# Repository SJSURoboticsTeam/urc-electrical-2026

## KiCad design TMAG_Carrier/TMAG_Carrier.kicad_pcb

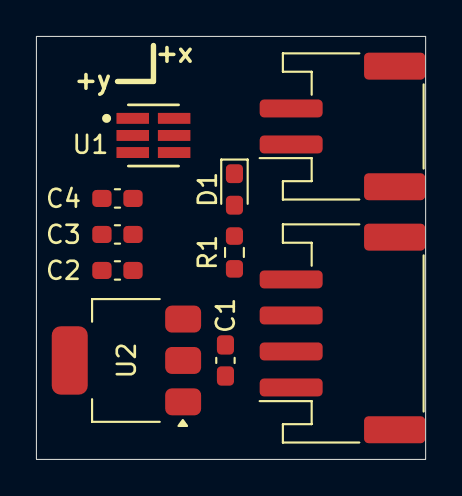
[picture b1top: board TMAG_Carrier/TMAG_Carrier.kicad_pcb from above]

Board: 2 copper layers, 21.6 x 23.5 mm, 10 parts (0 on the bottom side), 6 nets, no tracks yet.

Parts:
C1: 10u; C_0603_1608Metric_Pad1.08x0.95mm_HandSolder
C2: 22u; C_0603_1608Metric_Pad1.08x0.95mm_HandSolder
C3: 100n; C_0603_1608Metric_Pad1.08x0.95mm_HandSolder
C4: 1u; C_0603_1608Metric_Pad1.08x0.95mm_HandSolder
CanIn1: Conn_01x04_MountingPin; JST_PH_S4B-PH-SM4-TB_1x04-1MP_P2.00mm_Horizontal
D1: LED; LED_0603_1608Metric_Pad1.05x0.95mm_HandSolder
I2CIn1: Conn_01x02_MountingPin; JST_PH_S2B-PH-SM4-TB_1x02-1MP_P2.00mm_Horizontal
R1: 4.7k; R_0603_1608Metric_Pad0.98x0.95mm_HandSolder
U1: TMAG5273B1QDBVR; DBV0006A-IPC_A
U2: AMS1117-3.3; SOT-223-3_TabPin2

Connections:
+3V3: C2.1, C3.1, C4.1, R1.1, U1.4 (VCC), U2.2 (VO)
+5V: C1.1, CanIn1.1, U2.3 (VI)
GND: C1.2, C2.2, C3.2, C4.2, CanIn1.2, CanIn1.MP (MountPin), D1.1 (K), I2CIn1.MP (MountPin), U1.2 (TEST), U1.3 (GND), U1.5 (INT_N), U2.1 (GND)
I2C_SCL: I2CIn1.1, U1.1 (SCL)
I2C_SDA: I2CIn1.2, U1.6 (SDA)
unnamed: D1.2 (A), R1.2

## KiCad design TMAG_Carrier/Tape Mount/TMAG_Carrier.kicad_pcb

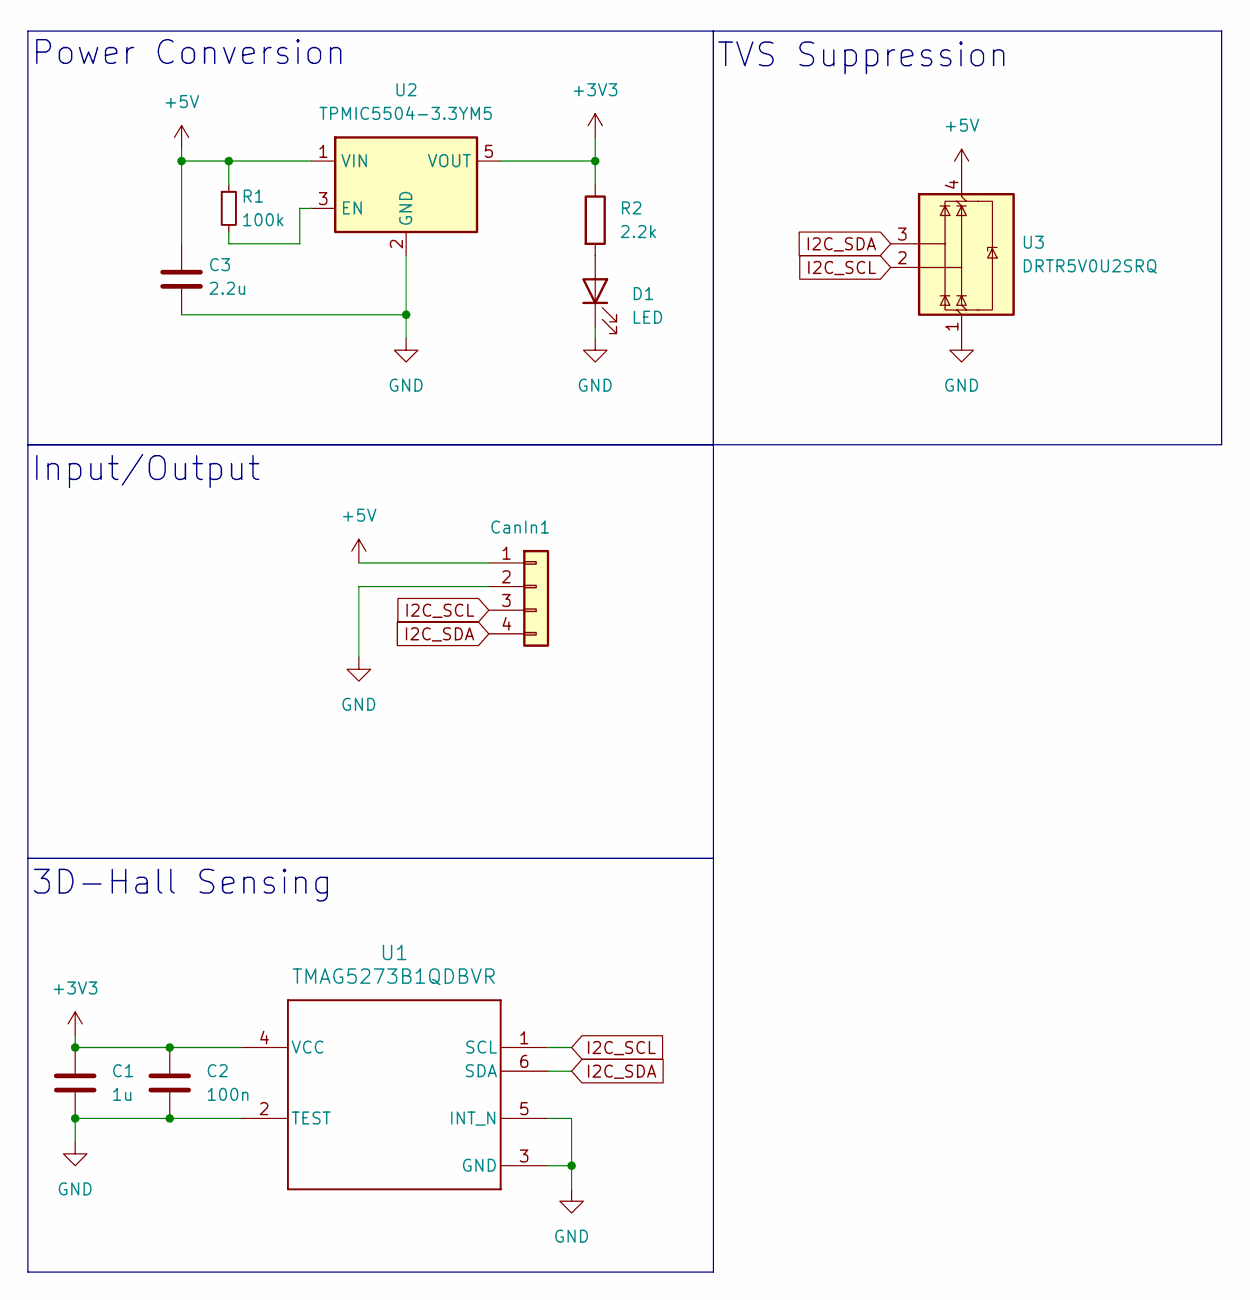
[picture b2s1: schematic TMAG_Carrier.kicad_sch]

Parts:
C1: 1u; C_0603_1608Metric_Pad1.08x0.95mm_HandSolder
C2: 100n; C_0603_1608Metric_Pad1.08x0.95mm_HandSolder
C3: 2.2u; C_0603_1608Metric_Pad1.08x0.95mm_HandSolder
CanIn1: Conn_01x04_MountingPin; Pluggable_Terminal_2.54mm_4P_Horizontal
D1: LED; LED_0603_1608Metric_Pad1.05x0.95mm_HandSolder
R1: 100k; R_0603_1608Metric_Pad0.98x0.95mm_HandSolder
R2: 2.2k; R_0603_1608Metric_Pad0.98x0.95mm_HandSolder
U1: TMAG5273B1QDBVR; DBV0006A-IPC_A
U2: TPMIC5504-3.3YM5; SOT-23-5
U3: DRTR5V0U2SRQ; SOT-143_Handsoldering

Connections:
+3V3: C1.1, C2.1, R2.1, U1.4 (VCC), U2.5 (VOUT)
+5V: C3.1, CanIn1.1, R1.1, U2.1 (VIN), U3.4 (VCC)
GND: C1.2, C2.2, C3.2, CanIn1.2, D1.1 (K), U1.2 (TEST), U1.3 (GND), U1.5 (INT_N), U2.2 (GND), U3.1 (GND)
I2C_SCL: CanIn1.3, U1.1 (SCL), U3.2 (I/O3)
I2C_SDA: CanIn1.4, U1.6 (SDA), U3.3 (I/O2)
unnamed: D1.2 (A), R2.2
unnamed: R1.2, U2.3 (EN)

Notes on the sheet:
Power Conversion
TVS Suppression
3D-Hall Sensing
Input/Output

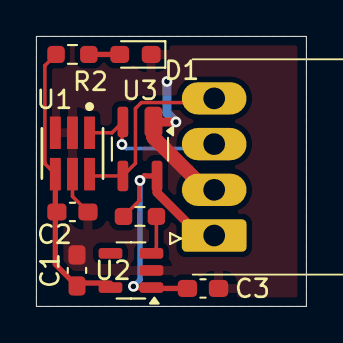
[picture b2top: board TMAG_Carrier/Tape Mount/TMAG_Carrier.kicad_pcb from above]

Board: 2 copper layers, 15.0 x 15.0 mm, 10 parts (0 on the bottom side), 7 nets.

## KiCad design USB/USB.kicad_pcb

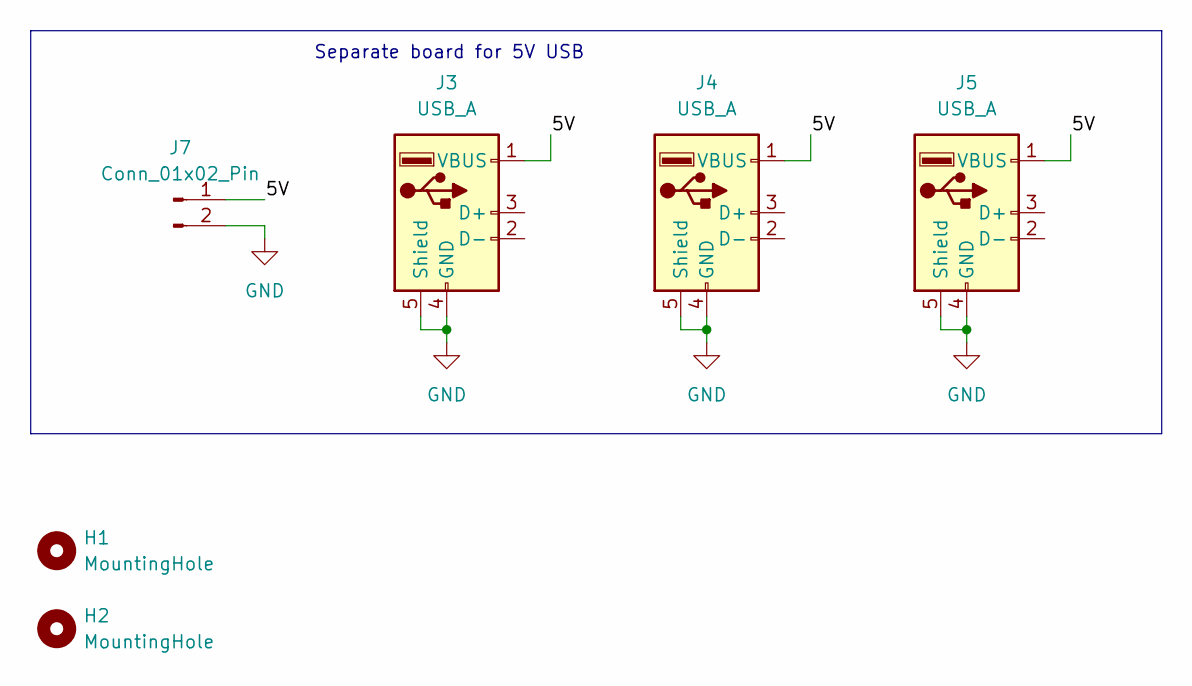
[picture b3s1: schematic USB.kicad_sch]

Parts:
H1, H2: MountingHole; MountingHole_3.2mm_M3_DIN965
J3, J4, J5: USB_A; USB_A_Molex_67643_Horizontal
J7: Conn_01x02_Pin; Pluggable_Terminal_2.54mm_2P_Horizontal

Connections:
/5V: J3.1 (VBUS), J4.1 (VBUS), J5.1 (VBUS), J7.1
GND: J3.4 (GND), J3.5 (Shield), J4.4 (GND), J4.5 (Shield), J5.4 (GND), J5.5 (Shield), J7.2

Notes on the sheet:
Separate board for 5V USB

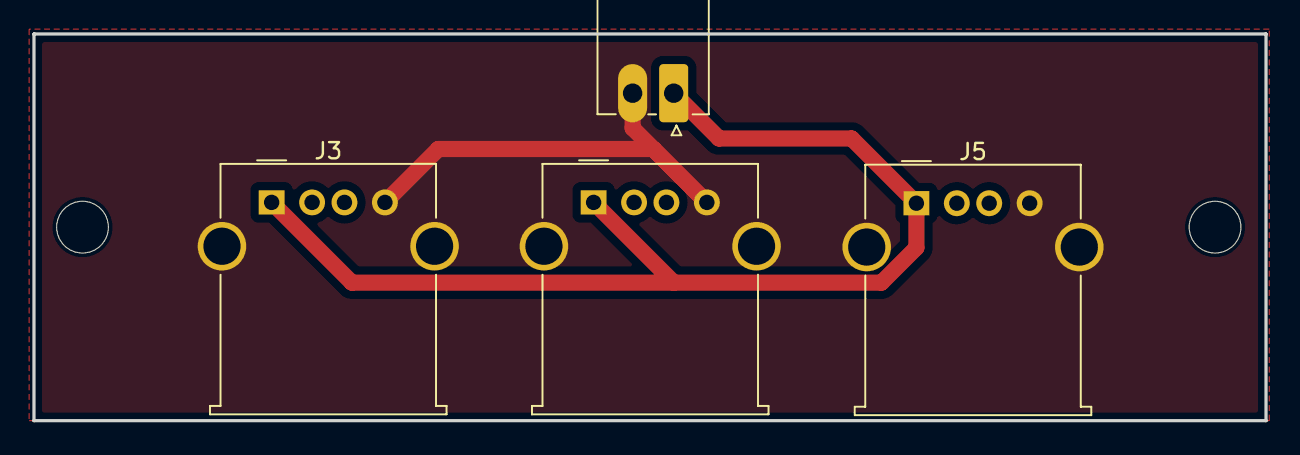
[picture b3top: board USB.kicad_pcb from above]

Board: 2 copper layers, 76.1 x 23.9 mm, 6 parts (0 on the bottom side), 2 nets.

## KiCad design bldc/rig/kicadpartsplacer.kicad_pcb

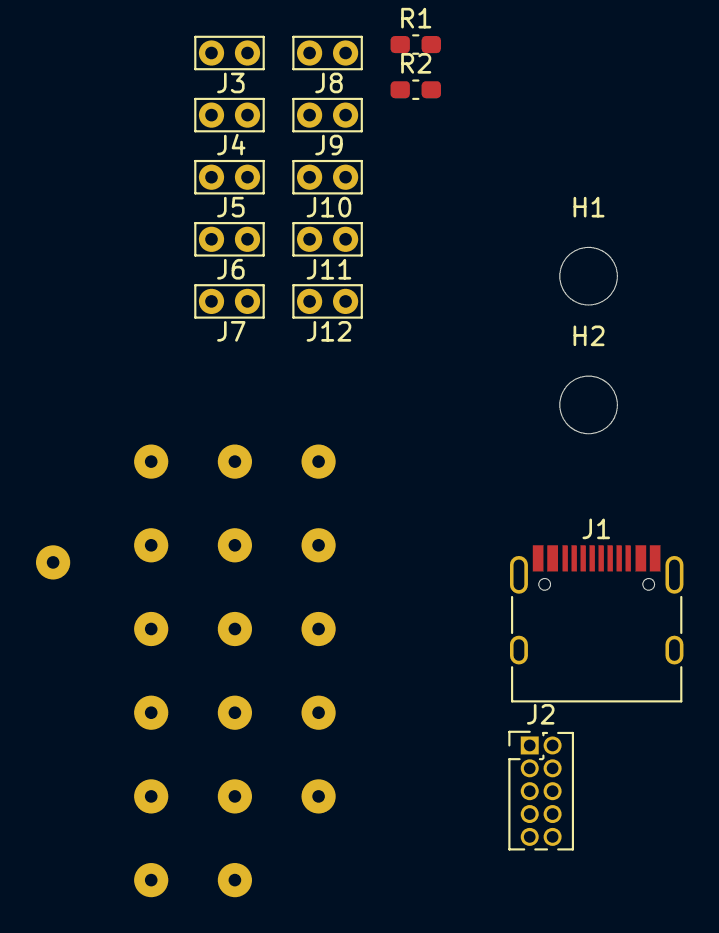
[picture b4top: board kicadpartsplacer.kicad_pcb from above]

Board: 2 copper layers, 34 parts (0 on the bottom side), 19 nets, no tracks yet.

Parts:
H1, H2: MountingHole; MountingHole_3.2mm_M3_DIN965
J1: USB_C_Receptacle_USB2.0_16P; USB_C_Receptacle_HRO_TYPE-C-31-M-12
J2: Conn_ARM_JTAG_SWD_10; PinHeader_2x05_P1.27mm_Vertical
J3, J4, J5, J6, J7, J8, J9, J10, J11, J12: Conn_01x01_Socket; TestPoint_Bridge_Pitch2.0mm_Drill0.7mm
R1, R2: 5.1k; C_0603_1608Metric_Pad1.08x0.95mm_HandSolder
TP1, TP2, TP3, TP4, TP5, TP6, TP7, TP8, TP9, TP10, TP11, TP12, TP13, TP14, TP15, TP16, TP17, TP18: 0906-0-15-20-76-14-11-0; MilMax_Pogo_0906-0-15-20-76-14-11-0

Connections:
+3V3: J5.1, TP9.1
+12V: J4.1, TP2.1
/CANH: J12.1, TP16.1
/CANL: J11.1, TP15.1
/CANRX: J9.1, TP12.1
/CANTX: J10.1, TP13.1
/D+: J1.A6 (D+), J1.B6 (D+), TP17.1
/D-: J1.A7 (D-), J1.B7 (D-), TP18.1
/RESET: J2.10 (~RESET), TP5.1
/SENSE1: J6.1, TP1.1
/SENSE2: J7.1, TP3.1
/SENSE3: J8.1, TP11.1
/SWDCK: J2.4 (SWCLK/TCK), TP6.1
/SWDIO: J2.2 (SWDIO/TMS), TP4.1
/SWDO: J2.6 (SWO/TDO), TP7.1
GND: J1.A1 (GND), J1.A12 (GND), J1.B1 (GND), J1.B12 (GND), J1.S1 (SHIELD), J2.3 (GND), J2.5 (GND), J3.1, R1.2, R2.1, TP10.1
unnamed: J1.A5 (CC1), R1.1
unnamed: J1.B5 (CC2), R2.2
VBUS: J1.A4 (VBUS), J1.A9 (VBUS), J1.B4 (VBUS), J1.B9 (VBUS)

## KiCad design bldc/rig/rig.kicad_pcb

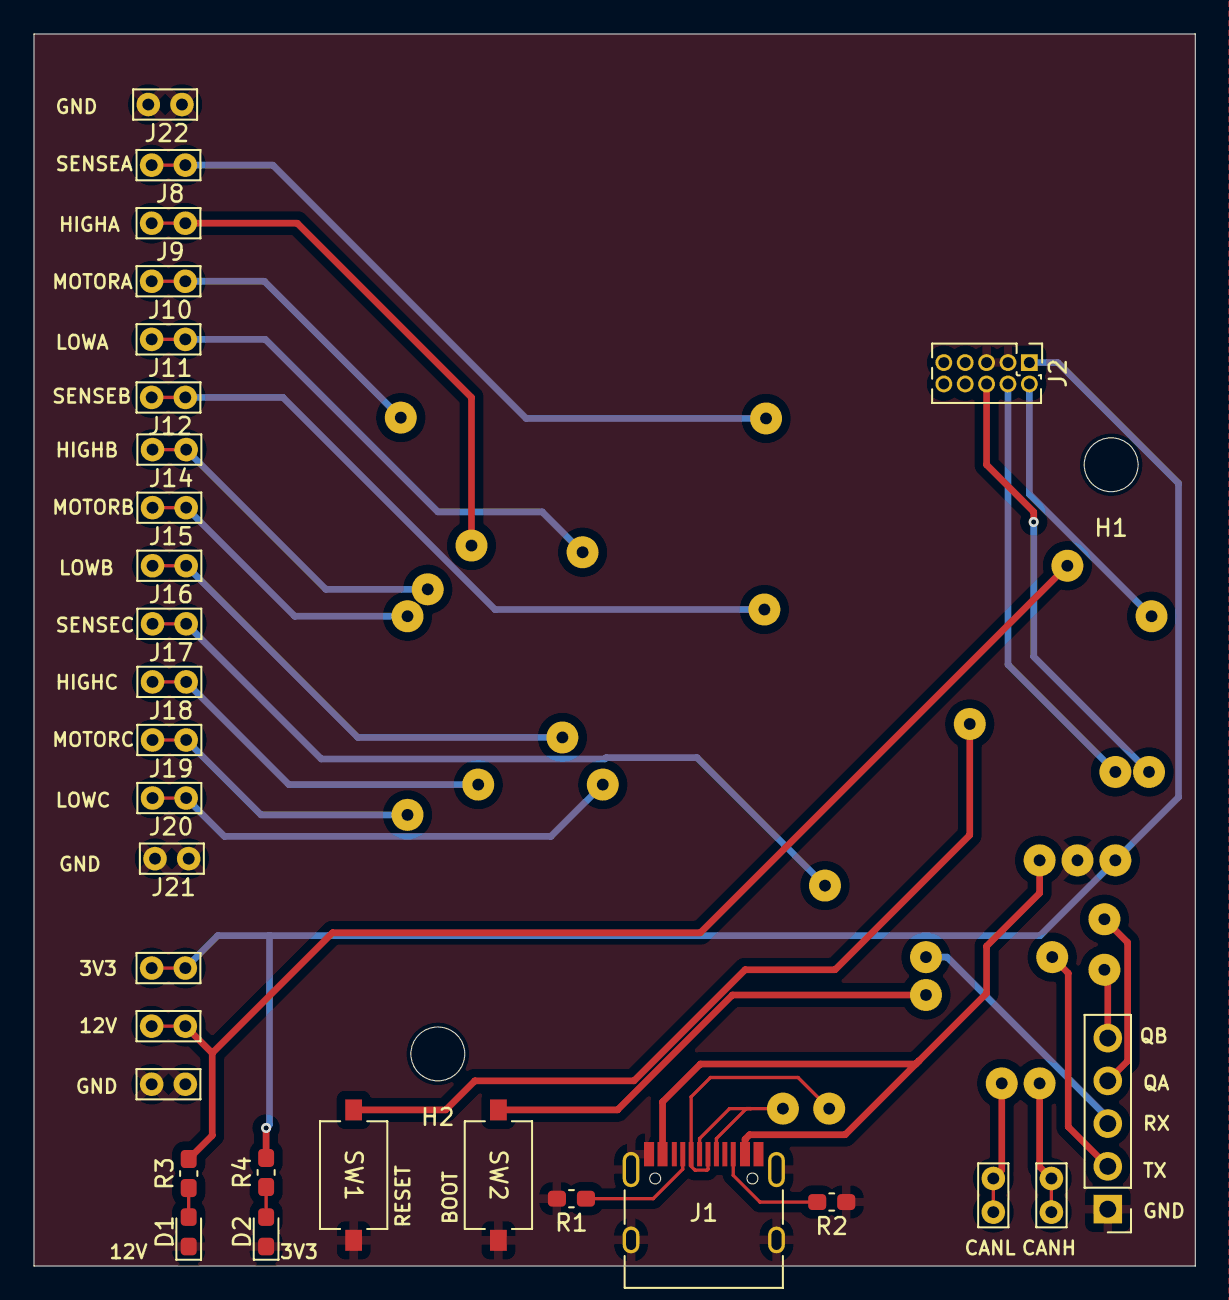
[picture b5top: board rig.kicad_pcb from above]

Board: 2 copper layers, 69.0 x 73.2 mm, 61 parts (0 on the bottom side), 33 nets.

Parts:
D1, D2: LED; LED_0603_1608Metric_Pad1.05x0.95mm_HandSolder
H1, H2: MountingHole; MountingHole_3.2mm_M3_DIN965
J1: USB_C_Receptacle_USB2.0_16P; USB_C_Receptacle_HRO_TYPE-C-31-M-12
J2: Conn_ARM_JTAG_SWD_10; PinHeader_2x05_P1.27mm_Vertical
J3, J4, J5, J6, J7, J8, J9, J10, J11, J12, J14, J15, J16, J17, J18, J19, J20, J21, J22: Conn_01x01_Socket; TestPoint_Bridge_Pitch2.0mm_Drill0.7mm
J13: Conn_01x05; PinHeader_1x05_P2.54mm_Vertical
R1, R2, R3, R4: 5.1k; C_0603_1608Metric_Pad1.08x0.95mm_HandSolder
SW1: RESET; SW_Tactile_SPST_NO_Straight_CK_PTS636Sx25SMTRLFS
SW2: BOOT; SW_Tactile_SPST_NO_Straight_CK_PTS636Sx25SMTRLFS
TP1, TP2, TP3, TP4, TP5, TP6, TP7, TP8, TP9, TP10, TP11, TP12, TP13, TP14, TP15, TP16, TP17, TP18, TP19, TP20, TP21, TP22, TP23, TP24, TP25, TP26, TP27, TP28, TP29: 0906-0-15-20-76-14-11-0; MilMax_Pogo_0906-0-15-20-76-14-11-0

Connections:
+3V3: J2.1 (VTref), J5.1, R4.2, TP6.1
+12V: J4.1, R3.2, TP5.1
/CANH: J7.1, TP12.1
/CANL: J6.1, TP13.1
/CAN_RX: J13.3, TP15.1
/CAN_TX: J13.2, TP14.1
/D+: J1.A6 (D+), J1.B6 (D+), TP3.1
/D-: J1.A7 (D-), J1.B7 (D-), TP4.1
/HIGHA: J9.1, TP19.1
/HIGHB: J14.1, TP23.1
/HIGHC: J18.1, TP27.1
/LOWA: J11.1, TP21.1
/LOWB: J16.1, TP25.1
/LOWC: J20.1, TP29.1
/MOTORA: J10.1, TP20.1
/MOTORB: J15.1, TP24.1
/MOTORC: J19.1, TP28.1
/QUADA: J13.4, TP16.1
/QUADB: J13.5, TP17.1
/SENSEA: J8.1, TP18.1
/SENSEB: J12.1, TP22.1
/SENSEC: J17.1, TP26.1
/SWDCK: J2.4 (SWCLK/TCK), TP9.1
/SWDIO: J2.2 (SWDIO/TMS), TP10.1
/SWO: J2.6 (SWO/TDO), TP11.1
/~BOOT: SW2.1, TP8.1
/~RESET: SW1.1, TP7.1
GND: D1.1 (K), D2.1 (K), J1.A1 (GND), J1.A12 (GND), J1.B1 (GND), J1.B12 (GND), J1.S1 (SHIELD), J2.3 (GND), J2.5 (GND), J3.1, J13.1, J21.1, J22.1, R1.2, R2.1, SW1.2, SW2.2, TP1.1
unnamed: D1.2 (A), R3.1
unnamed: D2.2 (A), R4.1
unnamed: J1.A5 (CC1), R1.1
unnamed: J1.B5 (CC2), R2.2
VBUS: J1.A4 (VBUS), J1.A9 (VBUS), J1.B4 (VBUS), J1.B9 (VBUS), TP2.1

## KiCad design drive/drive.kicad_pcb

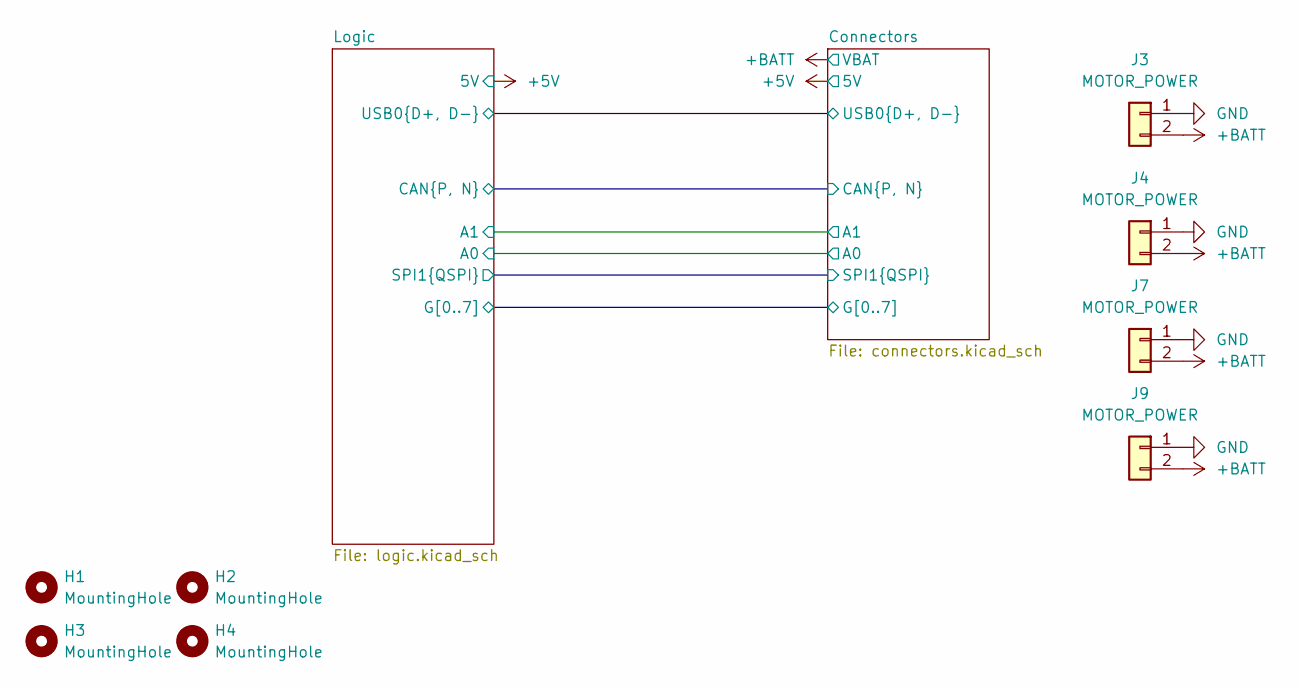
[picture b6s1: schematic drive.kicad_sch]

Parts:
H1, H2, H3, H4: MountingHole; MountingHole_3.2mm_M3
J3, J4, J7, J9: MOTOR_POWER; AMASS_XT30PW-M_1x02_P2.50mm_Horizontal

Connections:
+BATT: J3.2, J4.2, J7.2, J9.2; also elsewhere on the board
GND: J3.1, J4.1, J7.1, J9.1; also elsewhere on the board

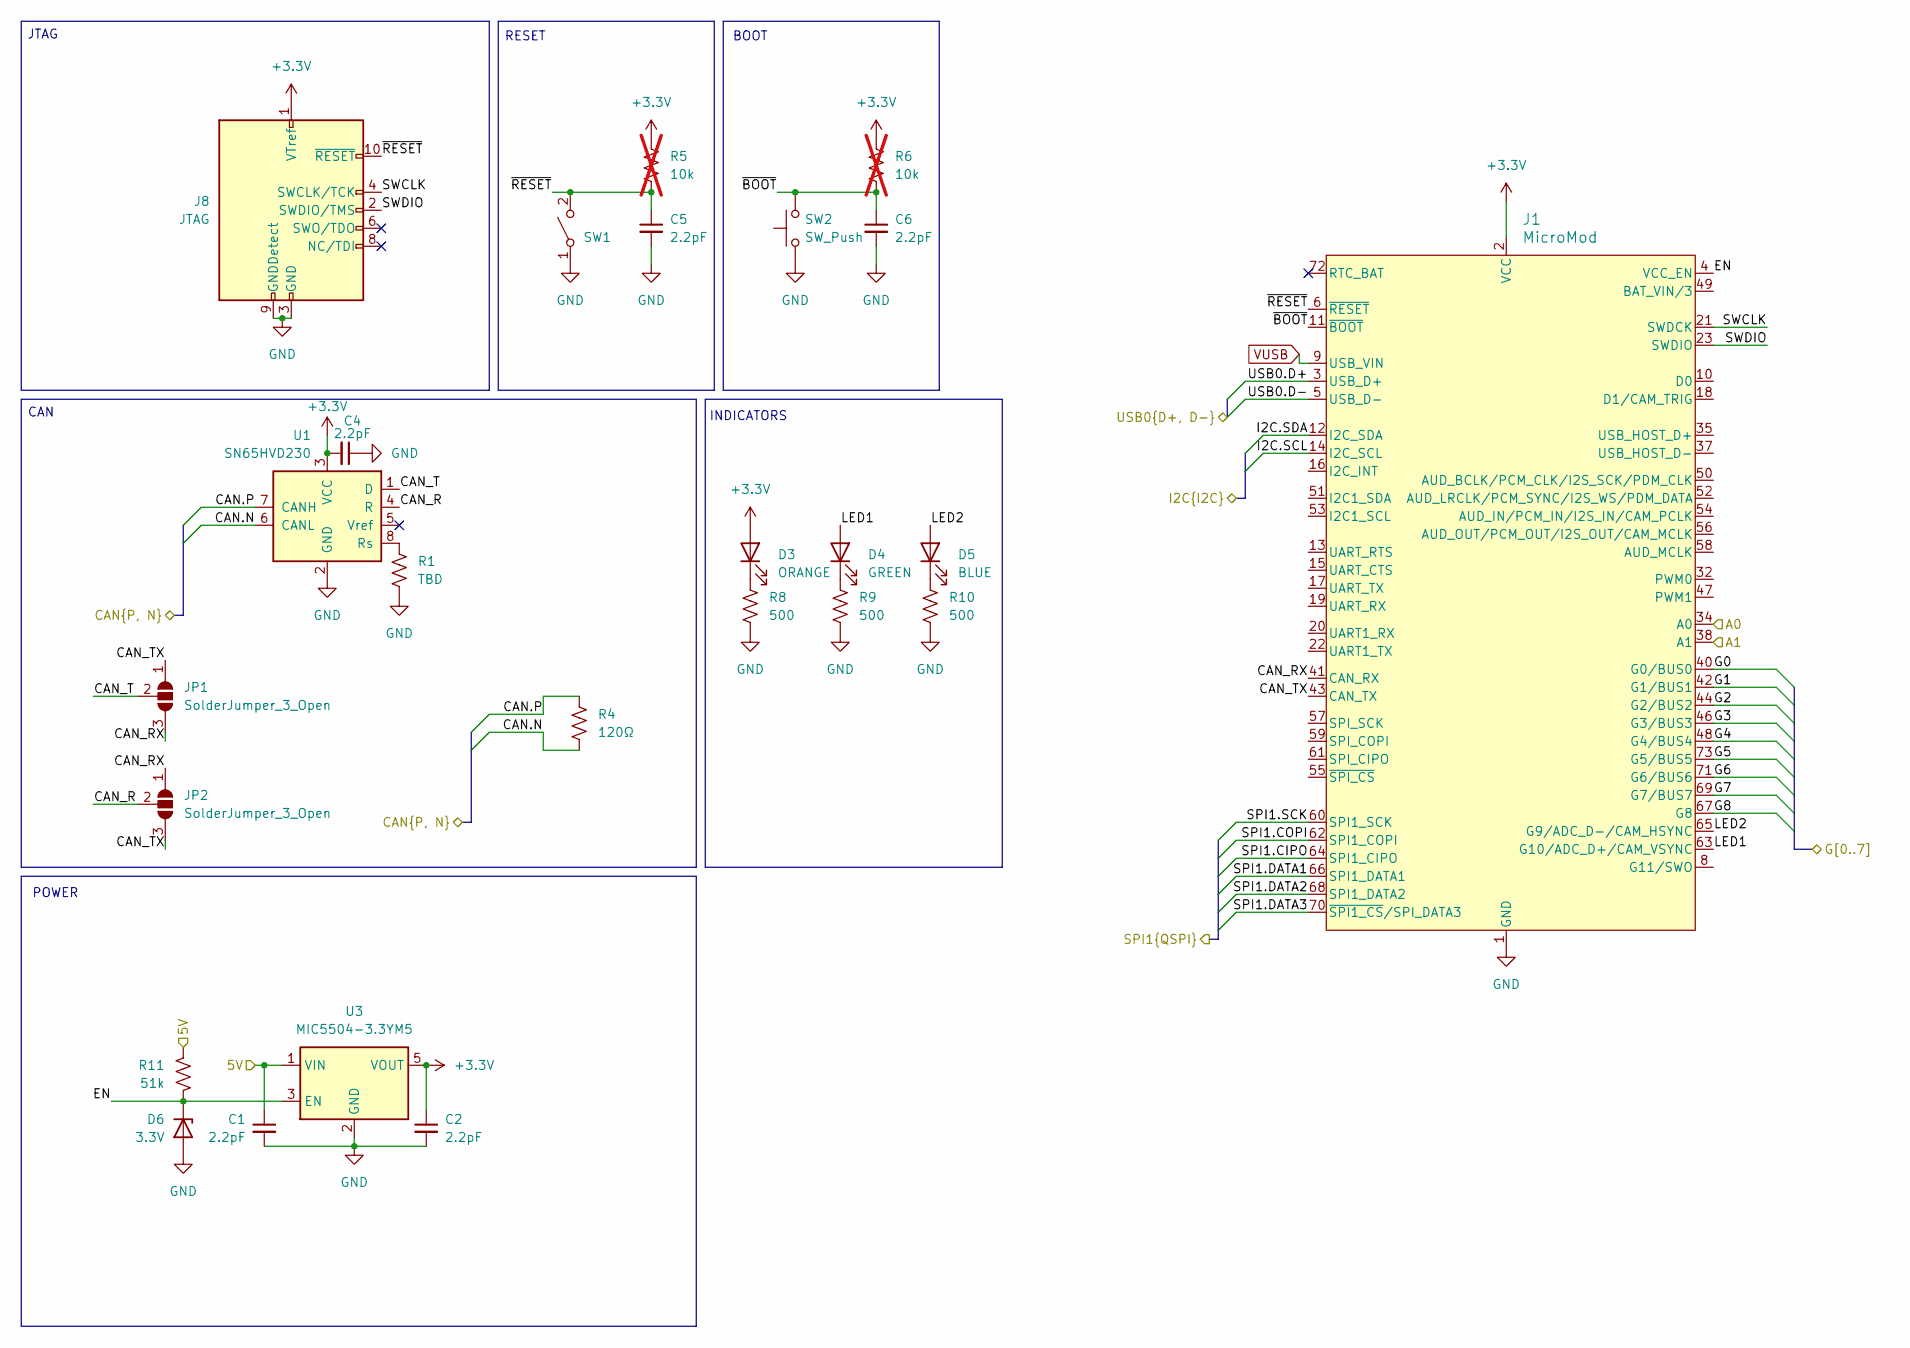
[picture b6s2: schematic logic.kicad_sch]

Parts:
C1, C2, C4, C5, C6: 2.2pF; C_0603_1608Metric_Pad1.08x0.95mm_HandSolder
D3: ORANGE; LED_0603_1608Metric_Pad1.05x0.95mm_HandSolder
D4: GREEN; LED_0603_1608Metric_Pad1.05x0.95mm_HandSolder
D5: BLUE; LED_0603_1608Metric_Pad1.05x0.95mm_HandSolder
D6: 3.3V; D_SMA
J1: MicroMod; micromod
J8: JTAG; PinHeader_2x05_P1.27mm_Vertical
JP1, JP2: SolderJumper_3_Open; SolderJumper-3_P1.3mm_Open_RoundedPad1.0x1.5mm
R1: TBD; R_0603_1608Metric
R4: 120Ω; R_0603_1608Metric
R5, R6: 10k; R_0603_1608Metric; not fitted
R8, R9, R10: 500; R_0603_1608Metric
R11: 51k; R_0603_1608Metric
SW1: SW_SPST; PinHeader_1x02_P2.54mm_Vertical
SW2: SW_Push; SW_SPST_CK_RS282G05A3; Digikey # CKN10384TR-ND
U1: SN65HVD230; SOIC-8_3.9x4.9mm_P1.27mm; LCSC # C12084
U3: MIC5504-3.3YM5; SOT-23-5; LCSC # C88419

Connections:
+3.3V: C2.1, C4.2, D3.2 (A), J1.2 (VCC), J1.74 (VCC), J8.1 (VTref), R5.1, R6.1, U1.3 (VCC), U3.5 (VOUT); also elsewhere on the board
+5V: C1.1, R11.1, U3.1 (VIN); also elsewhere on the board
/Connectors/A0: J1.34 (A0); also elsewhere on the board
/Connectors/A1: J1.38 (A1); also elsewhere on the board
/Connectors/CAN.N: R4.2, U1.6 (CANL); also elsewhere on the board
/Connectors/CAN.P: R4.1, U1.7 (CANH); also elsewhere on the board
/Connectors/G0: J1.40 (G0/BUS0); also elsewhere on the board
/Connectors/G1: J1.42 (G1/BUS1); also elsewhere on the board
/Connectors/G2: J1.44 (G2/BUS2); also elsewhere on the board
/Connectors/G3: J1.46 (G3/BUS3); also elsewhere on the board
/Connectors/G4: J1.48 (G4/BUS4); also elsewhere on the board
/Connectors/G5: J1.73 (G5/BUS5); also elsewhere on the board
/Connectors/G6: J1.71 (G6/BUS6); also elsewhere on the board
/Connectors/G7: J1.69 (G7/BUS7); also elsewhere on the board
/Connectors/I2C.SCL: J1.14 (I2C_SCL); also elsewhere on the board
/Connectors/I2C.SDA: J1.12 (I2C_SDA); also elsewhere on the board
/Connectors/SPI1.CIPO: J1.64 (SPI1_CIPO); also elsewhere on the board
/Connectors/SPI1.COPI: J1.62 (SPI1_COPI); also elsewhere on the board
/Connectors/SPI1.DATA1: J1.66 (SPI1_DATA1); also elsewhere on the board
/Connectors/SPI1.DATA2: J1.68 (SPI1_DATA2); also elsewhere on the board
/Connectors/SPI1.DATA3: J1.70 (~SPI1_CS/SPI_DATA3); also elsewhere on the board
/Connectors/SPI1.SCK: J1.60 (SPI1_SCK); also elsewhere on the board
/Connectors/USB0.D+: J1.3 (USB_D+); also elsewhere on the board
/Connectors/USB0.D-: J1.5 (USB_D-); also elsewhere on the board
/Logic/CAN_R: JP2.2 (C), U1.4 (R)
/Logic/CAN_RX: J1.41 (CAN_RX), JP1.3 (B), JP2.1 (A)
/Logic/CAN_T: JP1.2 (C), U1.1 (D)
/Logic/CAN_TX: J1.43 (CAN_TX), JP1.1 (A), JP2.3 (B)
/Logic/EN: D6.1 (K), J1.4 (VCC_EN), R11.2, U3.3 (EN)
/Logic/G8: J1.67 (G8)
/Logic/LED1: D4.2 (A), J1.63 (G10/ADC_D+/CAM_VSYNC)
/Logic/LED2: D5.2 (A), J1.65 (G9/ADC_D-/CAM_HSYNC)
/Logic/SWCLK: J1.21 (SWDCK), J8.4 (SWCLK/TCK)
/Logic/SWDIO: J1.23 (SWDIO), J8.2 (SWDIO/TMS)
/Logic/~BOOT: C6.1, J1.11 (~BOOT), R6.2, SW2.2
/Logic/~RESET: C5.1, J1.6 (~RESET), J8.10 (~RESET), R5.2, SW1.2 (B)
GND: C1.2, C2.2, C4.1, C5.2, C6.2, D6.2 (A), J1.1 (GND), J1.7 (GND), J1.33 (GND), J1.36 (GND), J1.39 (GND), J1.45 (GND), J1.75 (GND), J1.S1 (GND), J1.S2 (GND), J1.S3 (GND), J8.3 (GND), J8.5 (GND), J8.9 (GNDDetect), R1.2, R8.2, R9.2, R10.2, SW1.1 (A), SW2.1, U1.2 (GND), U3.2 (GND); also elsewhere on the board
unnamed: D3.1 (K), R8.1
unnamed: D4.1 (K), R9.1
unnamed: D5.1 (K), R10.1
unnamed: R1.1, U1.8 (Rs)

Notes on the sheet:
JTAG
CAN
RESET
INDICATORS
BOOT
POWER

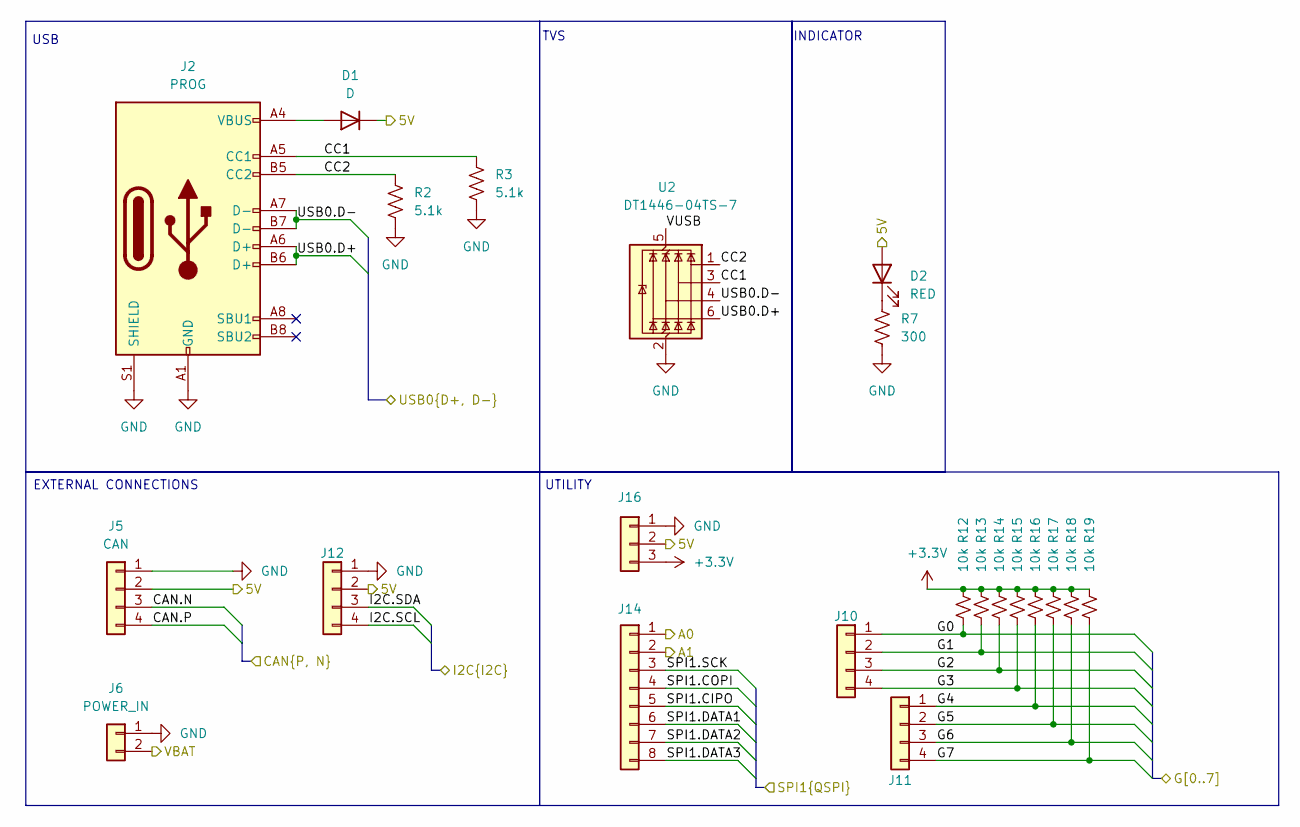
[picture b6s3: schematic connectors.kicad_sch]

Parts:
D1: D; Vishay_SMPA
D2: RED; LED_0603_1608Metric_Pad1.05x0.95mm_HandSolder
J2: PROG; USB_C_Receptacle_HRO_TYPE-C-31-M-12; LCSC # C165948
J5: CAN; Pluggable_Terminal_2.54mm_4P_Vertical
J6: POWER_IN; AMASS_XT60PW-M_1x02_P7.20mm_Horizontal
J10, J11, J12: Pluggable_Terminal_2.54mm_4P_Vertical
J14: Conn_01x08; PinHeader_1x08_P2.54mm_Vertical
J16: Conn_01x03; PinHeader_1x03_P2.54mm_Vertical
R2, R3: 5.1k; R_0603_1608Metric
R7: 300; R_0603_1608Metric
R12, R13, R14, R15, R16, R17, R18, R19: 10k; R_0603_1608Metric
U2: DT1446-04TS-7; SOT-23-6; LCSC # C19829509

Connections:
+3.3V: J16.3, R12.1, R13.1, R14.1, R15.1, R16.1, R17.1, R18.1, R19.1; also elsewhere on the board
+5V: D1.1 (K), D2.2 (A), J5.2, J12.2, J16.2; also elsewhere on the board
+BATT: J6.2; also elsewhere on the board
/Connectors/A0: J14.1; also elsewhere on the board
/Connectors/A1: J14.2; also elsewhere on the board
/Connectors/CAN.N: J5.3; also elsewhere on the board
/Connectors/CAN.P: J5.4; also elsewhere on the board
/Connectors/CC1: J2.A5 (CC1), R3.1, U2.3 (I/O2)
/Connectors/CC2: J2.B5 (CC2), R2.1, U2.1 (I/O1)
/Connectors/G0: J10.1, R12.2; also elsewhere on the board
/Connectors/G1: J10.2, R13.2; also elsewhere on the board
/Connectors/G2: J10.3, R14.2; also elsewhere on the board
/Connectors/G3: J10.4, R15.2; also elsewhere on the board
/Connectors/G4: J11.1, R16.2; also elsewhere on the board
/Connectors/G5: J11.2, R17.2; also elsewhere on the board
/Connectors/G6: J11.3, R18.2; also elsewhere on the board
/Connectors/G7: J11.4, R19.2; also elsewhere on the board
/Connectors/I2C.SCL: J12.4; also elsewhere on the board
/Connectors/I2C.SDA: J12.3; also elsewhere on the board
/Connectors/SPI1.CIPO: J14.5; also elsewhere on the board
/Connectors/SPI1.COPI: J14.4; also elsewhere on the board
/Connectors/SPI1.DATA1: J14.6; also elsewhere on the board
/Connectors/SPI1.DATA2: J14.7; also elsewhere on the board
/Connectors/SPI1.DATA3: J14.8; also elsewhere on the board
/Connectors/SPI1.SCK: J14.3; also elsewhere on the board
/Connectors/USB0.D+: J2.A6 (D+), J2.B6 (D+), U2.6 (I/O4); also elsewhere on the board
/Connectors/USB0.D-: J2.A7 (D-), J2.B7 (D-), U2.4 (I/O3); also elsewhere on the board
GND: J2.A1 (GND), J2.A12 (GND), J2.B1 (GND), J2.B12 (GND), J2.S1 (SHIELD), J5.1, J6.1, J12.1, J16.1, R2.2, R3.2, R7.2, U2.2 (GND); also elsewhere on the board
unnamed: D2.1 (K), R7.1

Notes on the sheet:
EXTERNAL CONNECTIONS
USB
TVS
UTILITY
INDICATOR

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
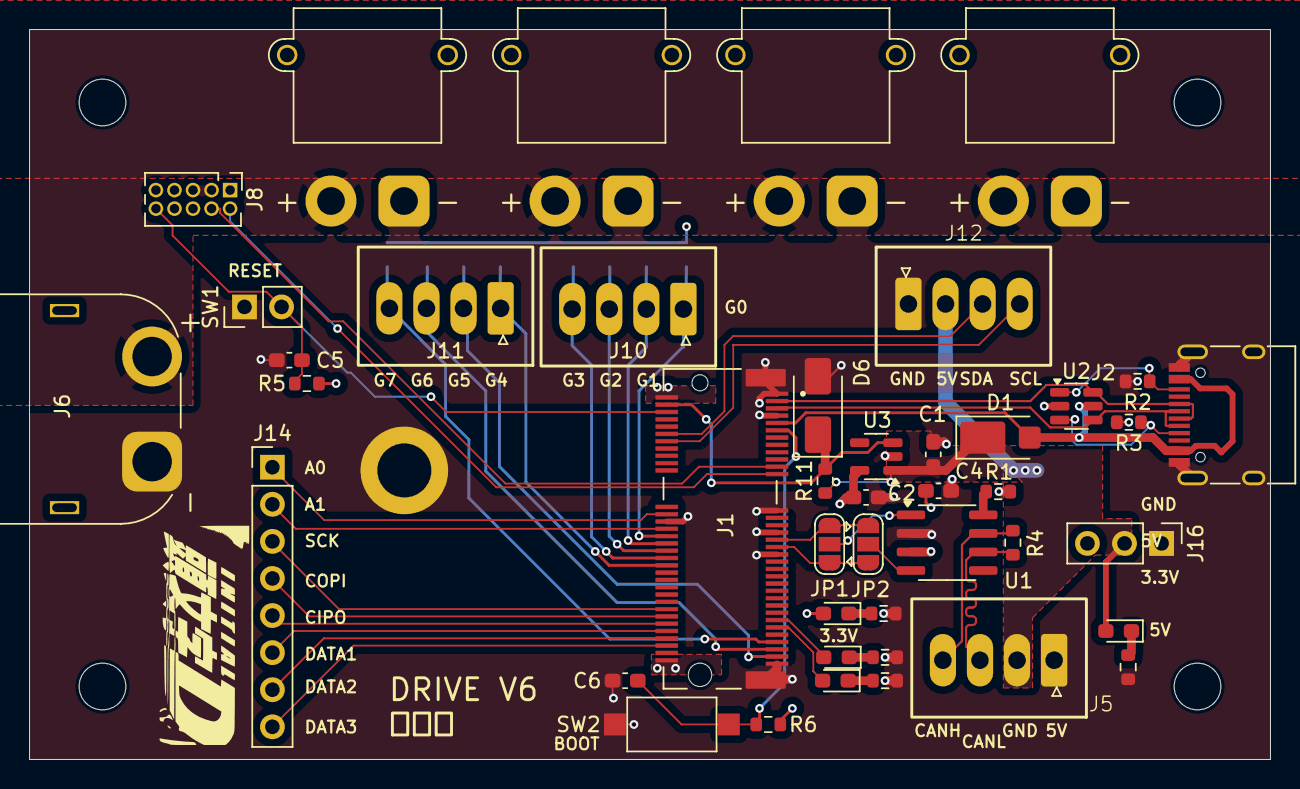
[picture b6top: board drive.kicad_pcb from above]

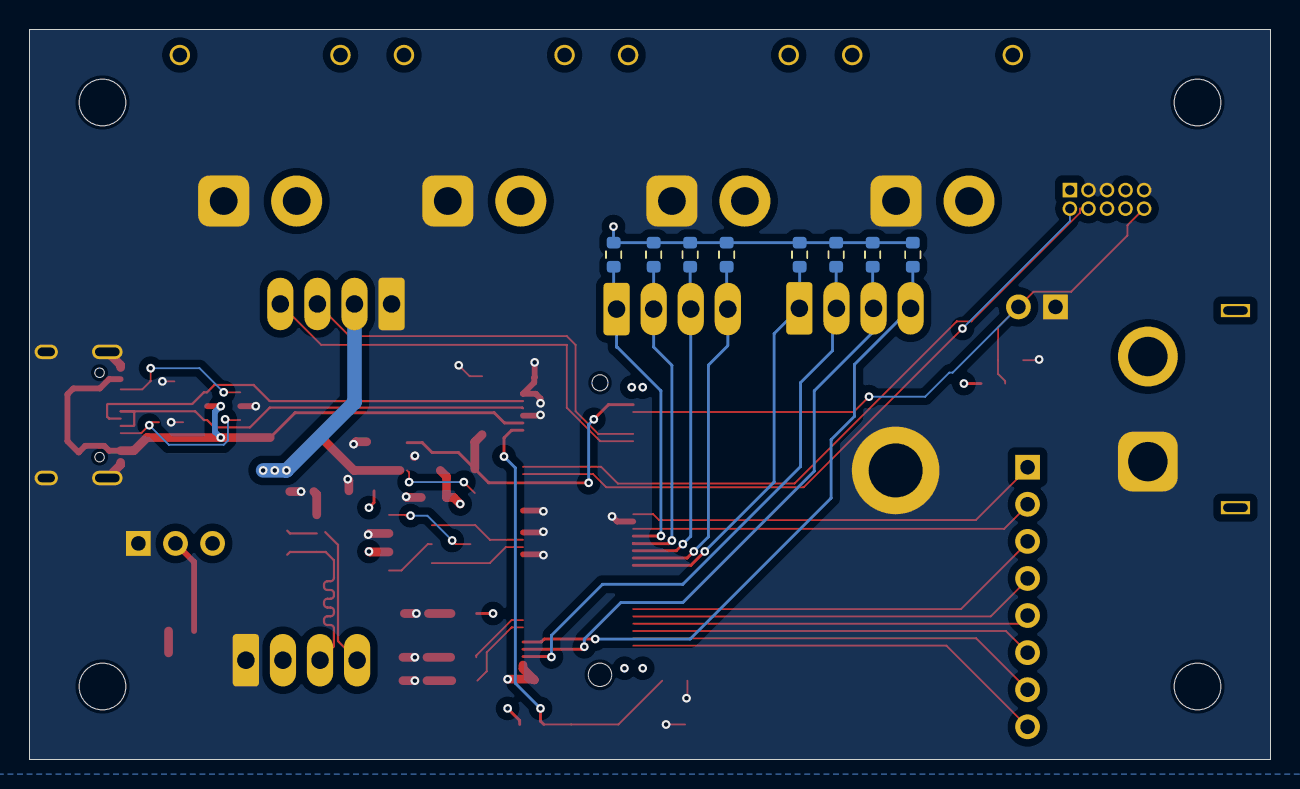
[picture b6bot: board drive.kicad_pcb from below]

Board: 4 copper layers, 85.0 x 50.0 mm, 55 parts (8 on the bottom side), 45 nets.
